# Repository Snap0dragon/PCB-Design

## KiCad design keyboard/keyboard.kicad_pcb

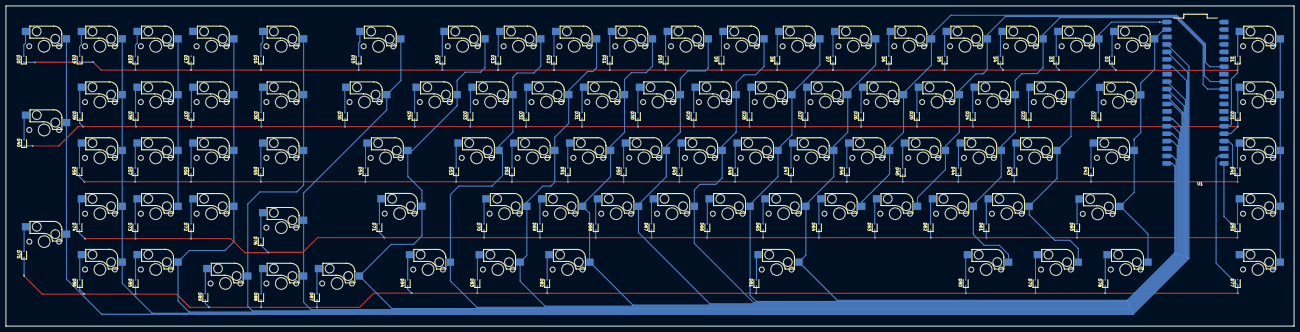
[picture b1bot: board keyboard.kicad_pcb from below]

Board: 2 copper layers, 439.7 x 109.3 mm, 179 parts (90 on the bottom side), 114 nets.

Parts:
D1, D2, D3, D4, D5, D6, D7, D8, D9, D10, D11, D12, D13, D14, D15, D16, D17, D18, D19, D20, D21, D22, D23, D24, D25, D26, D27, D28, D29, D30, D31, D32, D33, D34, D35, D36, D37, D38, D39, D40, D41, D42, D43, D44, D45, D46, D47, D48, D49, D50, D51, D52, D53, D54, D55, D56, D57, D58, D59, D60, D61, D62, D63, D64, D65, D66, D67, D68, D69, D70, D71, D72, D73, D74, D75, D76, D77, D78, D79, D80, D81, D82, D83, D84, D85, D86, D87, D88, D89: D_Small; D_SOD-323
MX1: ESC; SW_Cherry_MX_1.00u_PCB
MX2: `; SW_Cherry_MX_1.00u_PCB
MX3, MX72: 1; SW_Cherry_MX_1.00u_PCB
MX4, MX73: 2; SW_Cherry_MX_1.00u_PCB
MX5, MX74: 3; SW_Cherry_MX_1.00u_PCB
MX6, MX56: 4; SW_Cherry_MX_1.00u_PCB
MX7, MX57: 5; SW_Cherry_MX_1.00u_PCB
MX8, MX58: 6; SW_Cherry_MX_1.00u_PCB
MX9, MX37: 7; SW_Cherry_MX_1.00u_PCB
MX10, MX38: 8; SW_Cherry_MX_1.00u_PCB
MX11, MX39: 9; SW_Cherry_MX_1.00u_PCB
MX12, MX85: 0; SW_Cherry_MX_1.00u_PCB
MX13, MX20: -; SW_Cherry_MX_1.00u_PCB
MX14: =; SW_Cherry_MX_1.00u_PCB
MX15: BACKSPACE; SW_Cherry_MX_2.00u_PCB
MX16: DELETE; SW_Cherry_MX_1.00u_PCB
MX17: NUMLOCK; SW_Cherry_MX_1.00u_PCB
MX18, MX70: /; SW_Cherry_MX_1.00u_PCB
MX19: *; SW_Cherry_MX_1.00u_PCB
MX21: M0; SW_Cherry_MX_1.00u_PCB
MX22: TAB; SW_Cherry_MX_1.50u_PCB
MX23: Q; SW_Cherry_MX_1.00u_PCB
MX24: W; SW_Cherry_MX_1.00u_PCB
MX25: E; SW_Cherry_MX_1.00u_PCB
MX26: R; SW_Cherry_MX_1.00u_PCB
MX27: T; SW_Cherry_MX_1.00u_PCB
MX28: Y; SW_Cherry_MX_1.00u_PCB
MX29: U; SW_Cherry_MX_1.00u_PCB
MX30: I; SW_Cherry_MX_1.00u_PCB
MX31: O; SW_Cherry_MX_1.00u_PCB
MX32: P; SW_Cherry_MX_1.00u_PCB
MX33: [; SW_Cherry_MX_1.00u_PCB
MX34: ]; SW_Cherry_MX_1.00u_PCB
MX35: \; SW_Cherry_MX_1.50u_PCB
MX36: PGUP; SW_Cherry_MX_1.00u_PCB
MX40: +; SW_Cherry_MX_2.00u_Vertical_PCB
MX41: M1; SW_Cherry_MX_1.00u_PCB
MX42: CAPS LOCK; SW_Cherry_MX_1.75u_PCB
MX43: A; SW_Cherry_MX_1.00u_PCB
MX44: S; SW_Cherry_MX_1.00u_PCB
MX45: D; SW_Cherry_MX_1.00u_PCB
MX46: F; SW_Cherry_MX_1.00u_PCB
MX47: G; SW_Cherry_MX_1.00u_PCB
MX48: H; SW_Cherry_MX_1.00u_PCB
MX49: J; SW_Cherry_MX_1.00u_PCB
MX50: K; SW_Cherry_MX_1.00u_PCB
MX51: L; SW_Cherry_MX_1.00u_PCB
MX52: ;; SW_Cherry_MX_1.00u_PCB
MX53: '; SW_Cherry_MX_1.00u_PCB
MX54: ENTER; SW_Cherry_MX_2.25u_PCB
MX55: PGDN; SW_Cherry_MX_1.00u_PCB
MX59: M2; SW_Cherry_MX_1.00u_PCB
MX60: SHIFT; SW_Cherry_MX_2.25u_PCB
MX61: Z; SW_Cherry_MX_1.00u_PCB
MX62: X; SW_Cherry_MX_1.00u_PCB
MX63: C; SW_Cherry_MX_1.00u_PCB
MX64: V; SW_Cherry_MX_1.00u_PCB
MX65: B; SW_Cherry_MX_1.00u_PCB
MX66: N; SW_Cherry_MX_1.00u_PCB
MX67: M; SW_Cherry_MX_1.00u_PCB
MX68: ,; SW_Cherry_MX_1.00u_PCB
MX69, MX86: .; SW_Cherry_MX_1.00u_PCB
MX71: SHIFT; SW_Cherry_MX_2.75u_PCB
MX75: ENTER; SW_Cherry_MX_2.00u_Vertical_PCB
MX76: UP; SW_Cherry_MX_1.00u_PCB
MX77: M3; SW_Cherry_MX_1.00u_PCB
MX78, MX84: CTRL; SW_Cherry_MX_1.25u_PCB
MX79, MX82: ALT; SW_Cherry_MX_1.25u_PCB
MX80: WIN; SW_Cherry_MX_1.25u_PCB
MX81: SPACE; SW_Cherry_MX_6.25u_PCB
MX83: MENU; SW_Cherry_MX_1.25u_PCB
MX87: LEFT; SW_Cherry_MX_1.00u_PCB
MX88: DOWN; SW_Cherry_MX_1.00u_PCB
MX89: RIGHT; SW_Cherry_MX_1.00u_PCB
U1: RASPBERRY_PI_PICO; MODULE_RASPBERRY_PI_PICO_W

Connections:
COL0: MX1.1, MX21.1, MX41.1, MX59.1, MX77.1
COL1: MX2.1, MX22.1, MX42.1, MX60.1, MX78.1, U1.2 (GP1)
COL2: MX3.1, MX23.1, MX43.1, MX61.1, MX79.1, U1.1 (GP0)
COL3: MX4.1, MX24.1, MX44.1, MX62.1, MX80.1, U1.31 (GP26_A0)
COL4: MX5.1, MX25.1, MX45.1, MX63.1, U1.32 (GP27_A1)
COL5: MX6.1, MX26.1, MX46.1, MX64.1, U1.34 (GP28_A2)
COL6: MX7.1, MX27.1, MX47.1, MX65.1, MX81.1, U1.20 (GP15)
COL7: MX8.1, MX28.1, MX48.1, MX66.1, U1.19 (GP14)
COL8: MX9.1, MX29.1, MX49.1, MX67.1, U1.17 (GP13)
COL9: MX10.1, MX30.1, MX50.1, MX68.1, U1.16 (GP12)
COL10: MX11.1, MX31.1, MX51.1, MX69.1, MX82.1, U1.15 (GP11)
COL11: MX12.1, MX32.1, MX52.1, MX70.1, MX83.1, U1.14 (GP10)
COL12: MX13.1, MX33.1, MX53.1, MX84.1, U1.12 (GP9)
COL13: MX14.1, MX34.1, MX54.1, MX71.1, MX87.1, U1.11 (GP8)
COL14: MX15.1, MX35.1, MX76.1, MX88.1, U1.10 (GP7)
COL15: MX16.1, MX36.1, MX55.1, MX89.1, U1.9 (GP6)
COL16: MX17.1, MX37.1, MX56.1, MX72.1, MX85.1, U1.7 (GP5)
COL17: MX18.1, MX38.1, MX57.1, MX73.1, U1.6 (GP4)
COL18: MX19.1, MX39.1, MX58.1, MX74.1, MX86.1, U1.5 (GP3)
COL19: MX20.1, MX40.1, MX75.1, U1.4 (GP2)
unnamed: D1.2 (A), MX1.2
unnamed: D2.2 (A), MX2.2
unnamed: D3.2 (A), MX3.2
unnamed: D4.2 (A), MX4.2
unnamed: D5.2 (A), MX5.2
unnamed: D6.2 (A), MX6.2
unnamed: D7.2 (A), MX7.2
unnamed: D8.2 (A), MX8.2
unnamed: D9.2 (A), MX9.2
unnamed: D10.2 (A), MX10.2
unnamed: D11.2 (A), MX11.2
unnamed: D12.2 (A), MX12.2
unnamed: D13.2 (A), MX13.2
unnamed: D14.2 (A), MX14.2
unnamed: D15.2 (A), MX15.2
unnamed: D16.2 (A), MX16.2
unnamed: D17.2 (A), MX17.2
unnamed: D18.2 (A), MX18.2
unnamed: D19.2 (A), MX19.2
unnamed: D20.2 (A), MX20.2
unnamed: D21.2 (A), MX21.2
unnamed: D22.2 (A), MX22.2
unnamed: D23.2 (A), MX23.2
unnamed: D24.2 (A), MX24.2
unnamed: D25.2 (A), MX25.2
unnamed: D26.2 (A), MX26.2
unnamed: D27.2 (A), MX27.2
unnamed: D28.2 (A), MX28.2
unnamed: D29.2 (A), MX29.2
unnamed: D30.2 (A), MX30.2
unnamed: D31.2 (A), MX31.2
unnamed: D32.2 (A), MX32.2
unnamed: D33.2 (A), MX33.2
unnamed: D34.2 (A), MX34.2
unnamed: D35.2 (A), MX35.2
unnamed: D36.2 (A), MX36.2
unnamed: D37.2 (A), MX37.2
unnamed: D38.2 (A), MX38.2
unnamed: D39.2 (A), MX39.2
unnamed: D40.2 (A), MX40.2
unnamed: D41.2 (A), MX41.2
unnamed: D42.2 (A), MX42.2
unnamed: D43.2 (A), MX43.2
unnamed: D44.2 (A), MX44.2
unnamed: D45.2 (A), MX45.2
unnamed: D46.2 (A), MX46.2
unnamed: D47.2 (A), MX47.2
unnamed: D48.2 (A), MX48.2
unnamed: D49.2 (A), MX49.2
unnamed: D50.2 (A), MX50.2
unnamed: D51.2 (A), MX51.2
unnamed: D52.2 (A), MX52.2
unnamed: D53.2 (A), MX53.2
unnamed: D54.2 (A), MX54.2
unnamed: D55.2 (A), MX55.2
unnamed: D56.2 (A), MX56.2
unnamed: D57.2 (A), MX57.2
unnamed: D58.2 (A), MX58.2
unnamed: D59.2 (A), MX59.2
unnamed: D60.2 (A), MX60.2
unnamed: D61.2 (A), MX61.2
unnamed: D62.2 (A), MX62.2
unnamed: D63.2 (A), MX63.2
unnamed: D64.2 (A), MX64.2
unnamed: D65.2 (A), MX65.2
unnamed: D66.2 (A), MX66.2
unnamed: D67.2 (A), MX67.2
unnamed: D68.2 (A), MX68.2
unnamed: D69.2 (A), MX69.2
unnamed: D70.2 (A), MX70.2
unnamed: D71.2 (A), MX71.2
unnamed: D72.2 (A), MX72.2
unnamed: D73.2 (A), MX73.2
unnamed: D74.2 (A), MX74.2
unnamed: D75.2 (A), MX75.2
unnamed: D76.2 (A), MX76.2
unnamed: D77.2 (A), MX77.2
unnamed: D78.2 (A), MX78.2
unnamed: D79.2 (A), MX79.2
unnamed: D80.2 (A), MX80.2
unnamed: D81.2 (A), MX81.2
unnamed: D82.2 (A), MX82.2
unnamed: D83.2 (A), MX83.2
unnamed: D84.2 (A), MX84.2
unnamed: D85.2 (A), MX85.2
unnamed: D86.2 (A), MX86.2
unnamed: D87.2 (A), MX87.2
unnamed: D88.2 (A), MX88.2
unnamed: D89.2 (A), MX89.2
ROW0: D1.1 (K), D2.1 (K), D3.1 (K), D4.1 (K), D5.1 (K), D6.1 (K), D7.1 (K), D8.1 (K), D9.1 (K), D10.1 (K), D11.1 (K), D12.1 (K), D13.1 (K), D14.1 (K), D15.1 (K), D16.1 (K), D17.1 (K), D18.1 (K), D19.1 (K), D20.1 (K), U1.26 (GP20)
ROW1: D21.1 (K), D22.1 (K), D23.1 (K), D24.1 (K), D25.1 (K), D26.1 (K), D27.1 (K), D28.1 (K), D29.1 (K), D30.1 (K), D31.1 (K), D32.1 (K), D33.1 (K), D34.1 (K), D35.1 (K), D36.1 (K), D37.1 (K), D38.1 (K), D39.1 (K), D40.1 (K), U1.25 (GP19)
ROW2: D41.1 (K), D42.1 (K), D43.1 (K), D44.1 (K), D45.1 (K), D46.1 (K), D47.1 (K), D48.1 (K), D49.1 (K), D50.1 (K), D51.1 (K), D52.1 (K), D53.1 (K), D54.1 (K), D55.1 (K), D56.1 (K), D57.1 (K), D58.1 (K), U1.24 (GP18)
ROW3: D59.1 (K), D60.1 (K), D61.1 (K), D62.1 (K), D63.1 (K), D64.1 (K), D65.1 (K), D66.1 (K), D67.1 (K), D68.1 (K), D69.1 (K), D70.1 (K), D71.1 (K), D72.1 (K), D73.1 (K), D74.1 (K), D76.1 (K), U1.21 (GP16)
ROW4: D75.1 (K), D77.1 (K), D78.1 (K), D79.1 (K), D80.1 (K), D81.1 (K), D82.1 (K), D83.1 (K), D84.1 (K), D85.1 (K), D86.1 (K), D87.1 (K), D88.1 (K), D89.1 (K), U1.22 (GP17)

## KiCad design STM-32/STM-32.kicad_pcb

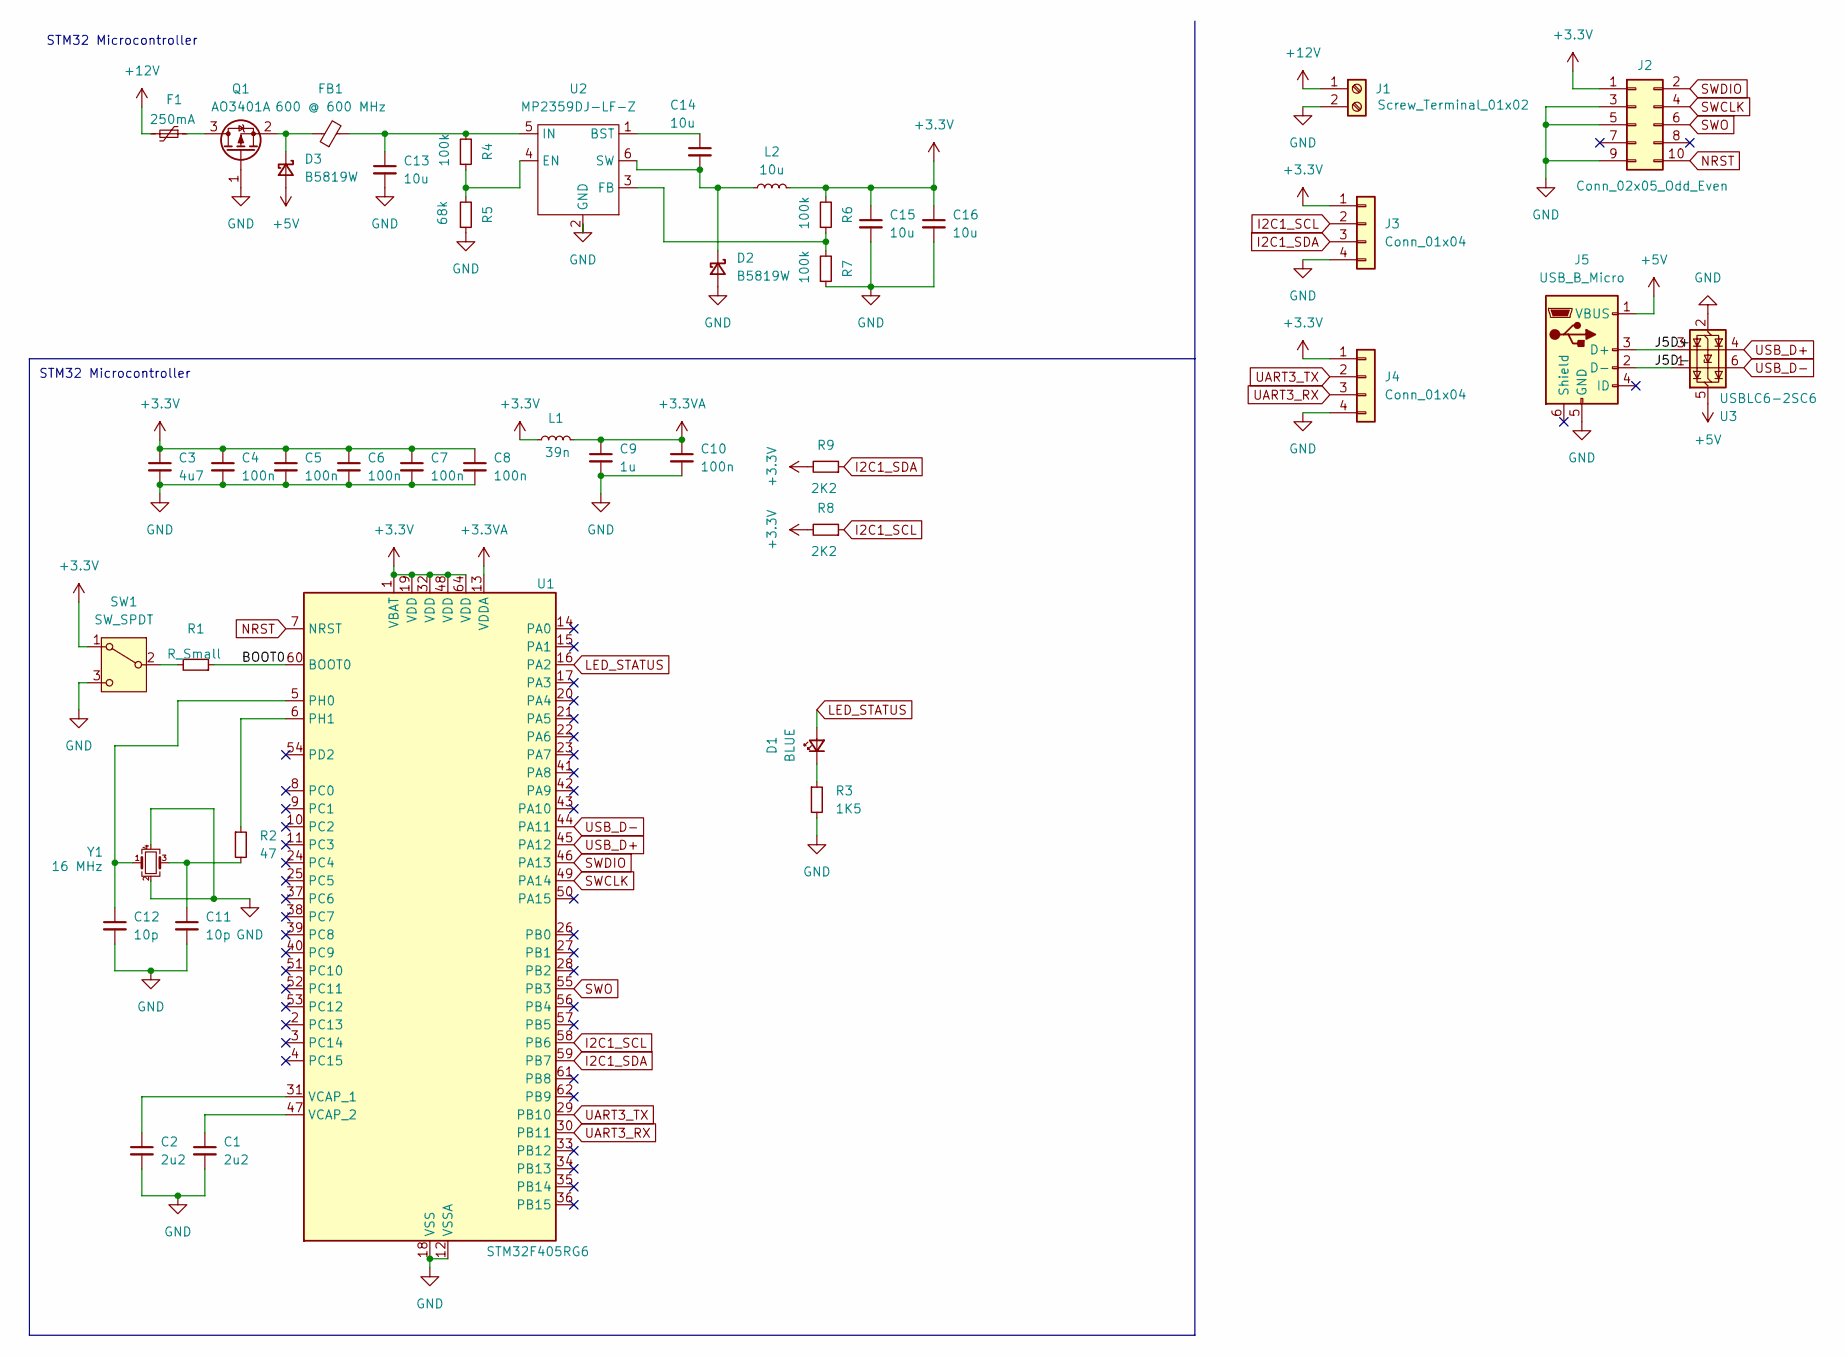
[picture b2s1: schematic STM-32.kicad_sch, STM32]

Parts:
C1, C2: 2u2; C_0603_1608Metric
C3: 4u7; C_0603_1608Metric
C4, C5, C6, C7, C8, C10: 100n; C_0402_1005Metric
C9: 1u; C_0402_1005Metric
C11, C12: 10p; C_0402_1005Metric
C13, C14, C15, C16: 10u; C_1206_3216Metric
D1: BLUE; LED_0603_1608Metric
D2, D3: B5819W; D_SOD-123
F1: 250mA; Fuse_1206_3216Metric
FB1: 600 @ 600 MHz; L_0805_2012Metric
J1: Screw_Terminal_01x02; TerminalBlock_Phoenix_PT-1,5-2-3.5-H_1x02_P3.50mm_Horizontal
J2: Conn_02x05_Odd_Even; PinSocket_2x05_P1.27mm_Vertical_SMD
J3, J4: Conn_01x04; Molex_PicoBlade_53048-0410_1x04_P1.25mm_Horizontal
J5: USB_B_Micro; USB_Micro-B_Amphenol_10118193-0001LF_Horizontal
L1: 39n; L_0402_1005Metric
L2: 10u; L_Sunlord_MWSA0518S
Q1: AO3401A; SOT-23
R1: R_Small; R_0402_1005Metric
R2: 47; R_0402_1005Metric
R3: 1K5; R_0603_1608Metric
R4, R6, R7: 100k; R_0603_1608Metric
R5: 68k; R_0603_1608Metric
R8, R9: 2K2; R_0603_1608Metric
SW1: SW_SPDT; SW_SPDT_PCM12
U1: STM32F405RG6; LQFP-64_10x10mm_P0.5mm
U2: MP2359DJ-LF-Z; SOT-23-6
U3: USBLC6-2SC6; SOT-23-6
Y1: 16 MHz; Crystal_SMD_3225-4Pin_3.2x2.5mm

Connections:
+3.3V: C3.1, C4.1, C5.1, C6.1, C7.1, C8.1, C15.1, C16.1, J2.1, J3.1, J4.1, L1.1, L2.2, R6.2, R8.2, R9.2, SW1.1 (A), U1.1 (VBAT), U1.19 (VDD), U1.32 (VDD), U1.48 (VDD), U1.64 (VDD)
+3.3VA: C9.1, C10.1, L1.2, U1.13 (VDDA)
+5V: D3.2 (A), J5.1 (VBUS), U3.5 (VBUS)
+12V: F1.2, J1.1
/BOOT0: R1.1, U1.60 (BOOT0)
/J5D+: J5.3 (D+), U3.3 (I/O2)
/J5D-: J5.2 (D-), U3.1 (I/O1)
GND: C1.2, C2.2, C3.2, C4.2, C5.2, C6.2, C7.2, C8.2, C9.2, C10.2, C11.2, C12.2, C13.2, C15.2, C16.2, D2.2 (A), J1.2, J2.3, J2.5, J2.9, J3.4, J4.4, J5.5 (GND), Q1.1 (G), R3.2, R5.1, R7.1, SW1.3 (C), U1.12 (VSSA), U1.18 (VSS), U1.63 (VSS), U2.2 (GND), U3.2 (GND), Y1.2, Y1.4
I2C1_SCL: J3.2, R8.1, U1.58 (PB6)
I2C1_SDA: J3.3, R9.1, U1.59 (PB7)
LED_STATUS: D1.2 (A), U1.16 (PA2)
NRST: J2.10, U1.7 (NRST)
unnamed: C11.1, R2.2, Y1.3
unnamed: D1.1 (K), R3.1
unnamed: C14.2, D2.1 (K), L2.1, U2.6 (SW)
unnamed: D3.1 (K), FB1.1, Q1.2 (S)
unnamed: F1.1, Q1.3 (D)
unnamed: R1.2, SW1.2 (B)
unnamed: C12.1, U1.5 (PH0), Y1.1
unnamed: R2.1, U1.6 (PH1)
unnamed: C2.1, U1.31 (VCAP_1)
unnamed: C1.1, U1.47 (VCAP_2)
unnamed: C14.1, U2.1 (BST)
unnamed: R4.1, R5.2, U2.4 (EN)
unnamed: R6.1, R7.2, U2.3 (FB)
unnamed: C13.1, FB1.2, R4.2, U2.5 (IN)
SWCLK: J2.4, U1.49 (PA14)
SWDIO: J2.2, U1.46 (PA13)
SWO: J2.6, U1.55 (PB3)
UART3_RX: J4.3, U1.30 (PB11)
UART3_TX: J4.2, U1.29 (PB10)
USB_D+: U1.45 (PA12), U3.4 (I/O2)
USB_D-: U1.44 (PA11), U3.6 (I/O1)

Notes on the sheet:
STM32 Microcontroller

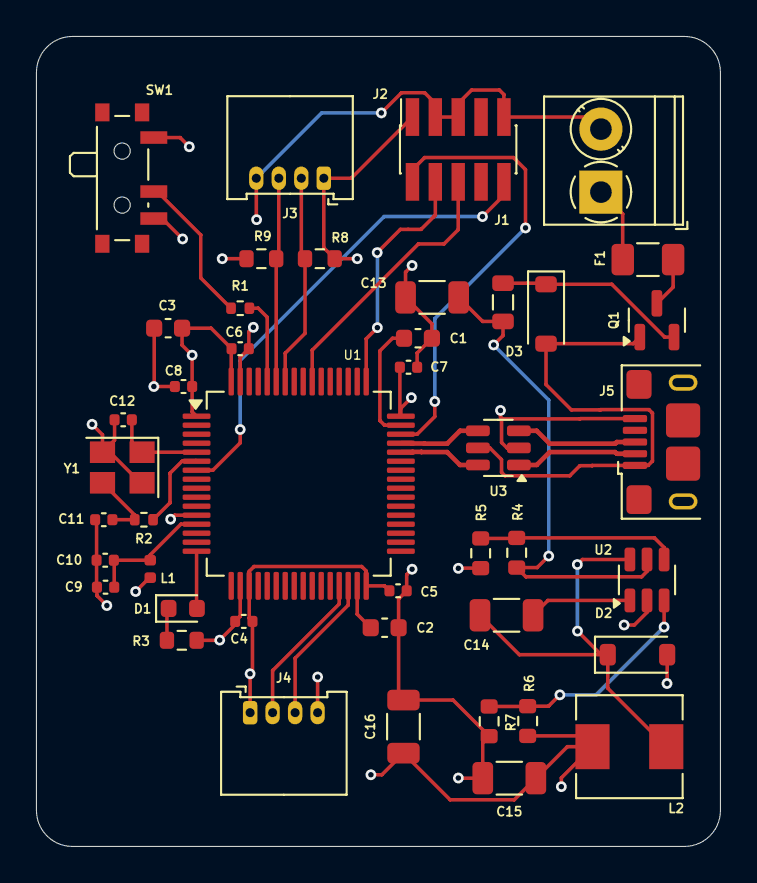
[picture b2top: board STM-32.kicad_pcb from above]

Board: 4 copper layers, 38.0 x 45.0 mm, 43 parts (0 on the bottom side), 33 nets.

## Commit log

2025-01-15 Create asd
2025-01-15 gnd edited
2025-02-02 keyboard design
2025-02-03 keyboard design new
2025-02-03 keyboard design - Routing V1
